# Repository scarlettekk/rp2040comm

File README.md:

# YARLoRa
_**Y**et **A**nother **R**P2040 **LoRa**_

This repository hosts project files for an RP2040-based microcontroller board with a LoRa 915MHz RFM95W transceiver and BLE5201 Bluetooth LE 5.2 module. 

v2 of the board has been completed but it has not yet been tested and there is no software for it yet.
This board was created for the Hack Club OnBoard program.

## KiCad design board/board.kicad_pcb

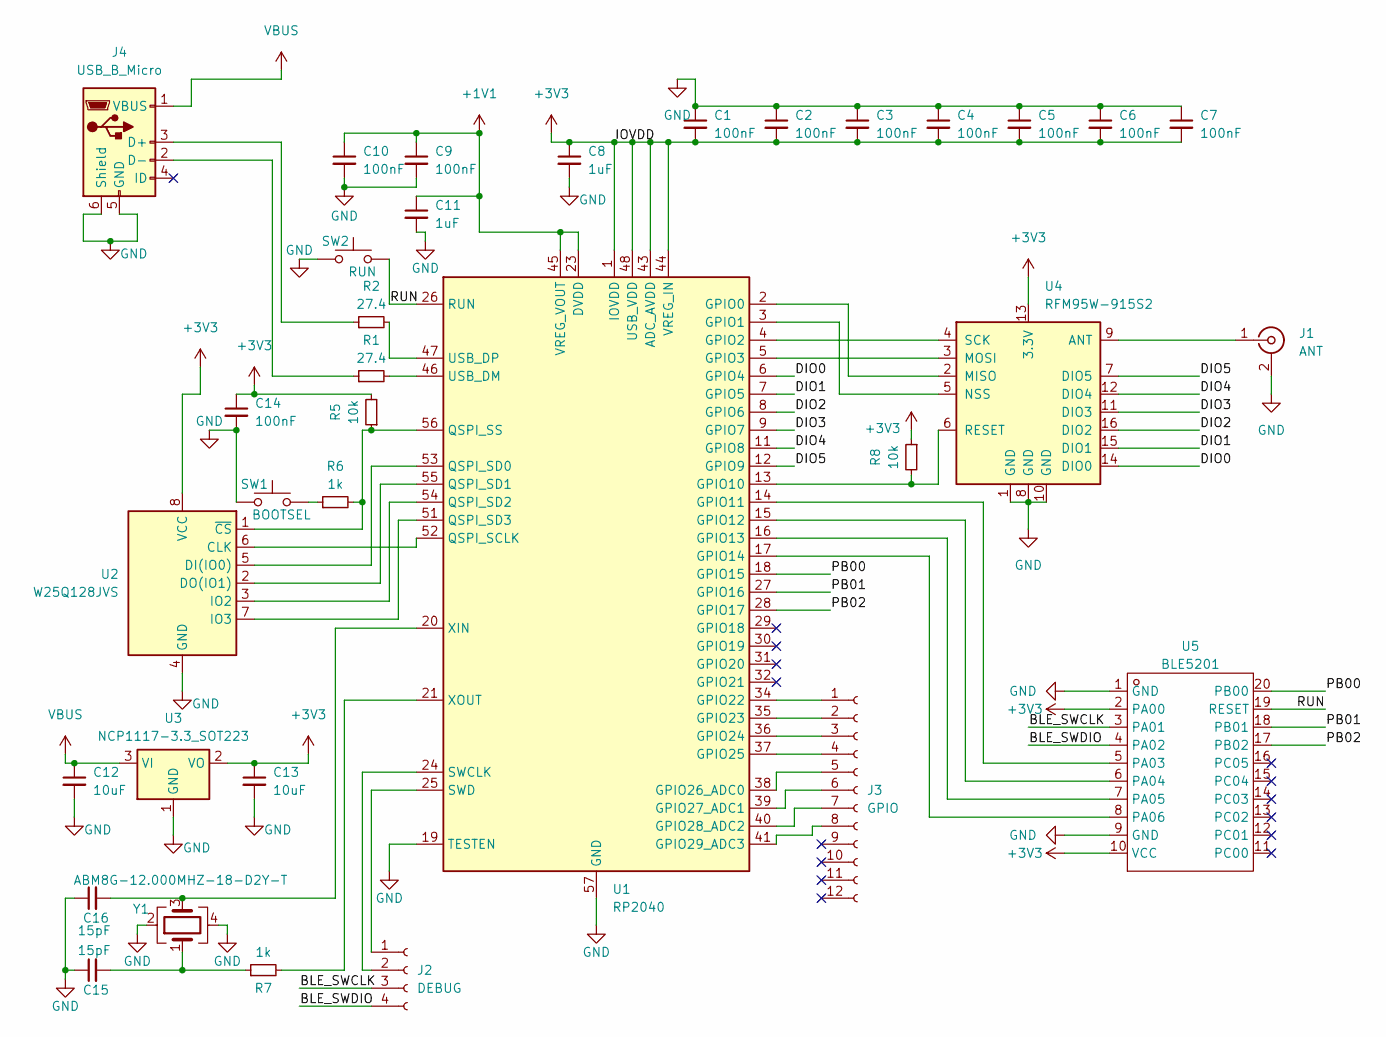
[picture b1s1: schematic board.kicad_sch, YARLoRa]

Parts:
C1, C2, C3, C4, C5, C6, C7, C9, C10, C14: 100nF; C_0402_1005Metric
C8, C11: 1uF; C_0402_1005Metric
C12, C13: 10uF; C_0402_1005Metric
C15, C16: 15pF; C_0402_1005Metric
J1: ANT; U.FL_Hirose_U.FL-R-SMT-1_Vertical
J2: DEBUG; PinSocket_1x04_P2.54mm_Vertical
J3: GPIO; PinSocket_1x12_P2.54mm_Vertical
J4: USB_B_Micro; USB_Micro-B_Amphenol_10118194_Horizontal
R1, R2: 27.4; R_0402_1005Metric
R5, R8: 10k; R_0402_1005Metric
R6, R7: 1k; R_0402_1005Metric
SW1: BOOTSEL; SW_Push_SPST_NO_Alps_SKRK
SW2: RUN; SW_Push_SPST_NO_Alps_SKRK
U1: RP2040; QFN-56-1EP_7x7mm_P0.4mm_EP3.2x3.2mm
U2: W25Q128JVS; SOIC-8_5.23x5.23mm_P1.27mm
U3: NCP1117-3.3_SOT223; SOT-223-3_TabPin2
U4: RFM95W-915S2; HOPERF_RFM9XW_SMD
U5: BLE5201; Manufacturer Part BLE5201
Y1: ABM8G-12.000MHZ-18-D2Y-T; Crystal_SMD_Abracon_ABM8G-4Pin_3.2x2.5mm

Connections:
+1V1: C9.1, C10.1, C11.1, U1.23 (DVDD), U1.45 (VREG_VOUT), U1.50 (DVDD)
+3V3: C1.2, C2.2, C3.2, C4.2, C5.2, C6.2, C7.2, C8.1, C13.1, C14.1, R5.2, R8.1, U1.1 (IOVDD), U1.10 (IOVDD), U1.22 (IOVDD), U1.33 (IOVDD), U1.42 (IOVDD), U1.43 (ADC_AVDD), U1.44 (VREG_IN), U1.48 (USB_VDD), U1.49 (IOVDD), U2.8 (VCC), U3.2 (OUTPUT), U4.13 (3.3V), U5.2 (PA00), U5.10 (VCC)
/BLE_SWCLK: J2.3, U5.3 (PA01)
/BLE_SWDIO: J2.4, U5.4 (PA02)
/DIO0: U1.6 (GPIO4), U4.14 (DIO0)
/DIO1: U1.7 (GPIO5), U4.15 (DIO1)
/DIO2: U1.8 (GPIO6), U4.16 (DIO2)
/DIO3: U1.9 (GPIO7), U4.11 (DIO3)
/DIO4: U1.11 (GPIO8), U4.12 (DIO4)
/DIO5: U1.12 (GPIO9), U4.7 (DIO5)
/PB00: U1.18 (GPIO15), U5.20 (PB00)
/PB01: U1.27 (GPIO16), U5.18 (PB01)
/PB02: U1.28 (GPIO17), U5.17 (PB02)
unnamed: C15.2, R7.1, Y1.1
unnamed: J2.1, U1.25 (SWD)
unnamed: J2.2, U1.24 (SWCLK)
unnamed: J3.1, U1.34 (GPIO22)
unnamed: J3.2, U1.35 (GPIO23)
unnamed: J3.3, U1.36 (GPIO24)
unnamed: J3.4, U1.37 (GPIO25)
unnamed: J3.5, U1.38 (GPIO26_ADC0)
unnamed: J3.6, U1.39 (GPIO27_ADC1)
unnamed: J3.7, U1.40 (GPIO28_ADC2)
unnamed: J3.8, U1.41 (GPIO29_ADC3)
unnamed: J4.3 (D+), R2.1
unnamed: J4.2 (D-), R1.1
unnamed: U1.2 (GPIO0), U4.2 (MISO)
unnamed: U1.3 (GPIO1), U4.5 (NSS)
unnamed: U1.4 (GPIO2), U4.4 (SCK)
unnamed: U1.5 (GPIO3), U4.3 (MOSI)
unnamed: R8.2, U1.13 (GPIO10), U4.6 (RESET)
unnamed: U1.14 (GPIO11), U5.5 (PA03)
unnamed: U1.15 (GPIO12), U5.6 (PA04)
unnamed: U1.16 (GPIO13), U5.7 (PA05)
unnamed: U1.17 (GPIO14), U5.8 (PA06)
unnamed: U1.52 (QSPI_SCLK), U2.6 (CLK)
unnamed: U1.53 (QSPI_SD0), U2.5 (DI(IO0))
unnamed: U1.55 (QSPI_SD1), U2.2 (DO(IO1))
unnamed: U1.54 (QSPI_SD2), U2.3 (IO2)
unnamed: U1.51 (QSPI_SD3), U2.7 (IO3)
unnamed: R5.1, R6.2, U1.56 (QSPI_SS), U2.1 (~CS)
unnamed: R1.2, U1.46 (USB_DM)
unnamed: R2.2, U1.47 (USB_DP)
unnamed: C16.2, U1.20 (XIN), Y1.3
unnamed: R7.2, U1.21 (XOUT)
unnamed: J1.1, U4.9 (ANT)
VBUS: C12.1, J4.1 (VBUS), U3.3 (INPUT)

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
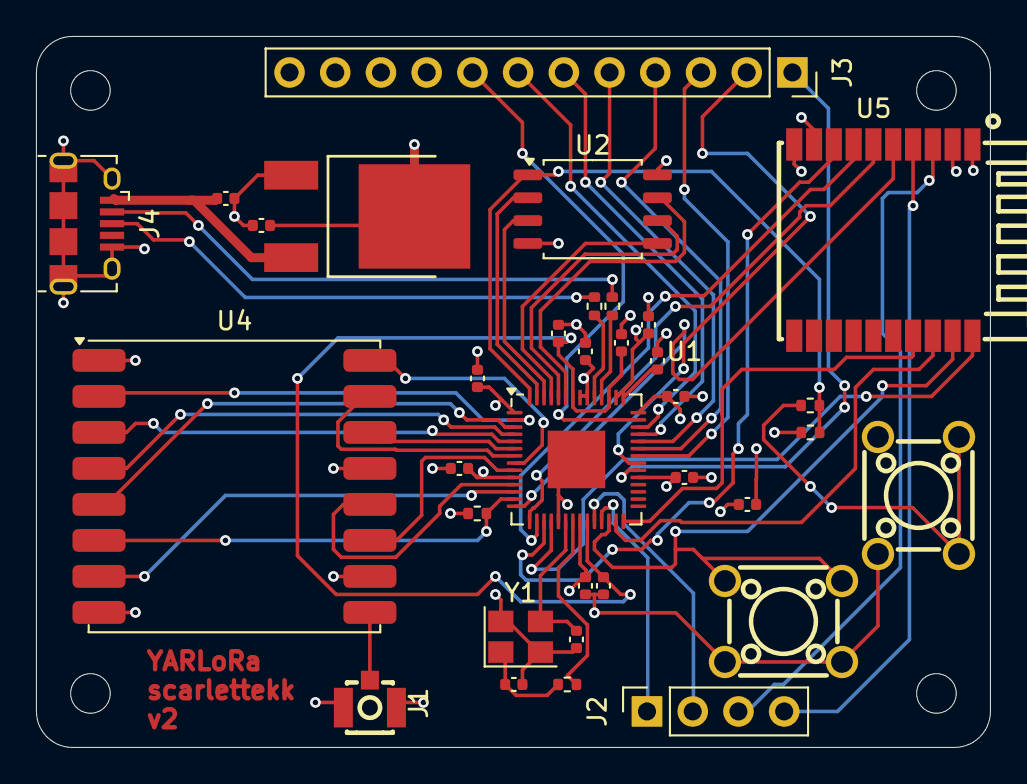
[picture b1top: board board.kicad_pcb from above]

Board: 4 copper layers, 53.0 x 39.5 mm, 34 parts (0 on the bottom side), 50 nets.

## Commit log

2024-07-25 add gitignore and initial IOVDD coupling
2024-07-25 DVDD
2024-07-25 Flash
2024-07-25 USB hopefully
2024-07-26 implement proper usb C
2024-07-26 voltage regulator
2024-07-26 flash resistors and BOOTSEL button
2024-07-27 crystal oscillator
2024-07-27 crystal footprint
2024-07-27 switch crystal for a better one
2024-07-27 LoRa PSI
2024-07-27 Finish LoRa schematic and add RUN button
2024-07-27 Appease ERC and add debug header
2024-07-28 board design: hr1
2024-07-28 board design: hr2
2024-07-31 board design v1
2024-07-31 add GPIO
2024-08-03 schematic v2 ft. ble, license under CC-BY-NC 4.0
2024-08-03 board v2 hour 1
2024-08-04 board v2 hour 2
2024-08-04 finish board v2
2024-08-04 appease jlcpcb (component swaps)
2024-08-04 notice
2024-08-06 add case
2024-08-06 fix case bottom

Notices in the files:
board/board.kicad_sch:
Licensed under CC BY-NC 4.0
